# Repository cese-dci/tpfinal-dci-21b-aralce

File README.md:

## Trabajo práctico final de la asignatura DCI ##
Este repositorio contiene el trabajo práctico final para la asignatura de Diseño de Circuitos Impresos de la carrera de posgrado de FIUBA.

* Autor: Ariel Cerfoglia
* Título corto del trabajo:  Fuente Protoboard
* Descripción:  Fuente para protoboar de 5v y 3.3v

## Licencia de este trabajo ##
GPLv2

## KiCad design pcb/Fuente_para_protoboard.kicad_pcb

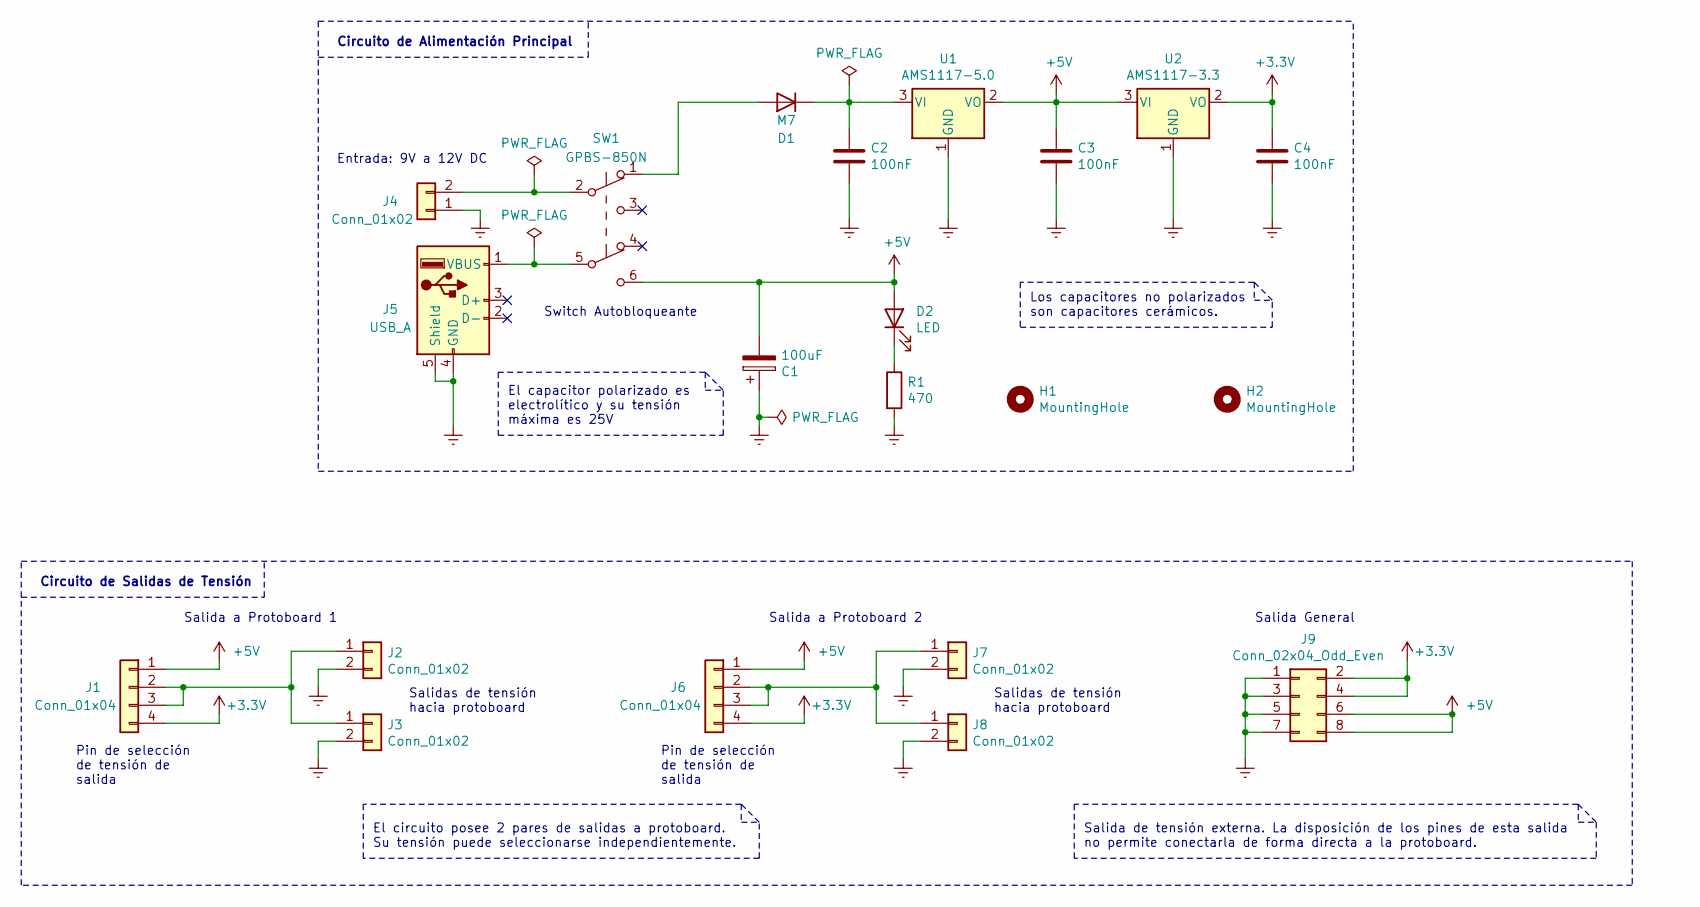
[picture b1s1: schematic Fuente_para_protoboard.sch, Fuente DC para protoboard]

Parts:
C1: 100uF; CP_Radial_D6.3mm_P2.50mm
C2, C3, C4: 100nF; C_0805_2012Metric
D1: M7; D_SMA
D2: LED; LED_D3.0mm
H1, H2: MountingHole; MountingHole_2.7mm
J1, J6: Conn_01x04; PinHeader_1x04_P2.54mm_Vertical
J2, J3, J7, J8: Conn_01x02; PinHeader_1x02_P2.54mm_Vertical
J4: Conn_01x02; BarrelJack_CUI_PJ-063AH_Horizontal
J5: USB_A; USB_A_Molex_67643_Horizontal
J9: Conn_02x04_Odd_Even; PinHeader_2x04_P2.54mm_Vertical
R1: 470; R_0805_2012Metric
SW1: GPBS-850N; GPBS850NR1
U1: AMS1117-5.0; SOT-223
U2: AMS1117-3.3; SOT-223

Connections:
+3V3: C4.1, J1.4, J6.4, J9.2, J9.4, U2.2 (VO)
+5V: C1.2, C3.1, D2.2 (A), J1.1, J6.1, J9.6, J9.8, SW1.6 (C), U1.2 (VO), U2.3 (VI)
Earth: C1.1, C2.2, C3.2, C4.2, J2.2, J3.2, J4.1, J5.4 (GND), J5.5 (Shield), J7.2, J8.2, J9.1, J9.3, J9.5, J9.7, R1.2, U1.1 (GND), U2.1 (GND)
unnamed: C2.1, D1.1 (K), U1.3 (VI)
unnamed: D1.2 (A), SW1.1 (A)
unnamed: D2.1 (K), R1.1
unnamed: J1.2, J1.3, J2.1, J3.1
unnamed: J4.2, SW1.2 (B)
unnamed: J5.1 (VBUS), SW1.5 (B)
unnamed: J6.2, J6.3, J7.1, J8.1

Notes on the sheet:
Circuito de Alimentación Principal
Pin de selección de tensión de salida
Salidas de tensión hacia protoboard
El circuito posee 2 pares de salidas a protoboard. Su tensión puede seleccionarse independientemente.
Salida de tensión externa. La disposición de los pines de esta salida no permite conectarla de forma directa a la protoboard.
Circuito de Salidas de Tensión
Switch Autobloqueante
Entrada: 9V a 12V DC
Los capacitores no polarizados son capacitores cerámicos.
El capacitor polarizado es electrolítico y su tensión máxima es 25V
Salida General
Salida a Protoboard 2
Salida a Protoboard 1

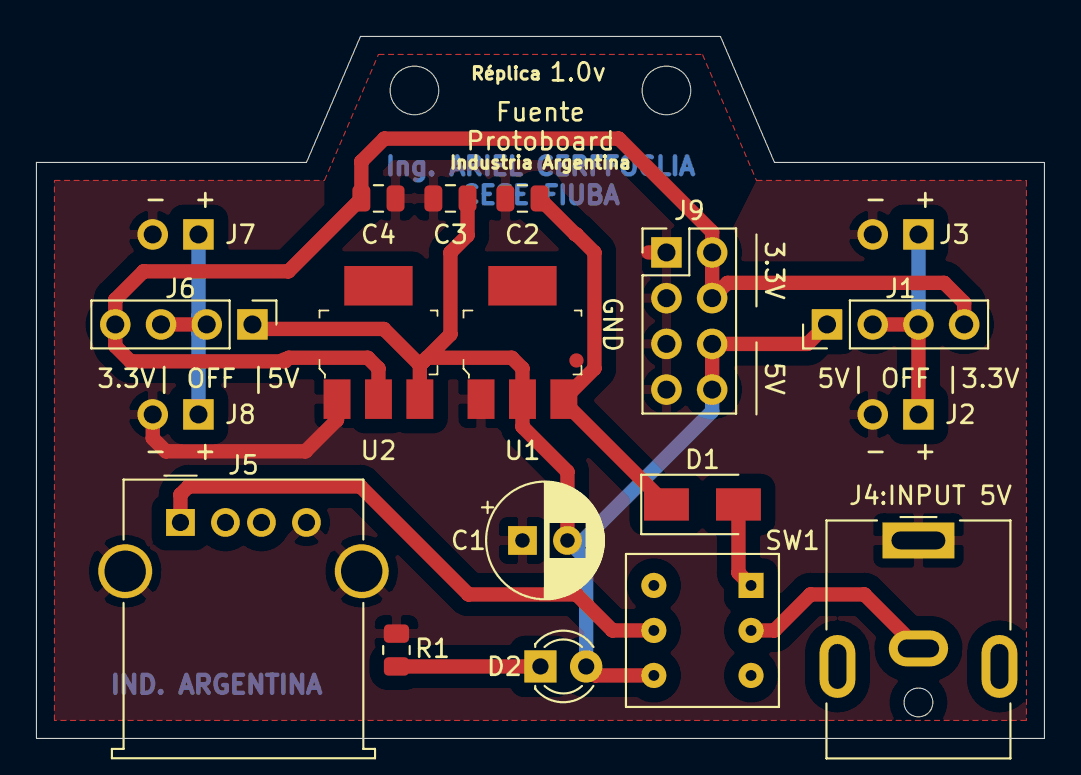
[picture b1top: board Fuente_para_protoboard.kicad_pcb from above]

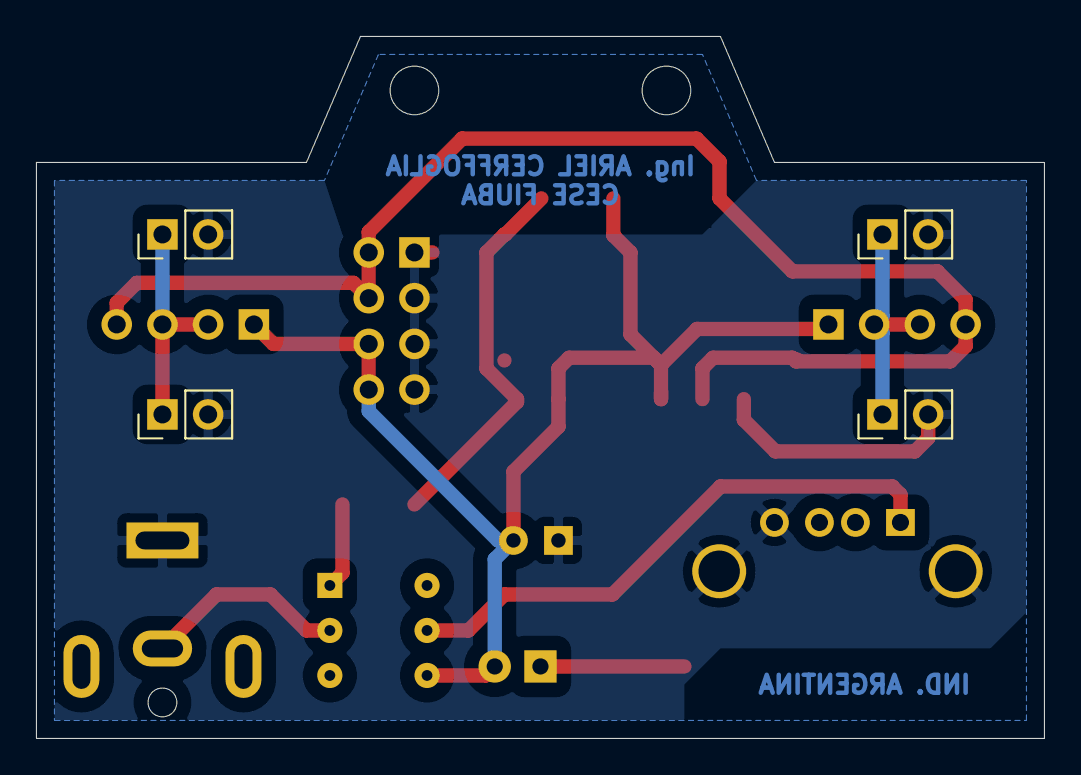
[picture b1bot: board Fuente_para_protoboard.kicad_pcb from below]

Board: 2 copper layers, 56.0 x 39.0 mm, 21 parts (4 on the bottom side), 10 nets.

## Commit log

2021-07-10 Se incorpora esquematico
2021-07-27 Huellas, posicionamiento, modelos 3D y ruteo
2021-08-16 Correcciones realizadas

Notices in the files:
pcb/Fuente_para_protoboard.sch:
Licencia: GPLv3
